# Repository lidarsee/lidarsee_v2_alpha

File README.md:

# LIDARsee v2 Hardware 

A good summary of the _Neato XV-11 LIDAR module_ can be found at:  
http://blog.tkjelectronics.dk/2014/08/handheld-xv-11-lidar-with-stm32f429-and-matlab/

## License
**Hardware license**: Creative Commons CC0
https://creativecommons.org/publicdomain/zero/1.0/legalcode

**Software license**: MIT License

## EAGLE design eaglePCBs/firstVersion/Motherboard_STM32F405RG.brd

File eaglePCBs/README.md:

# lidarsee_v2_hardware
Motherboard_STM32F405RG_r1 ist the mainboard for the head unit. 

### Features
* XV-11 lidar compatible
* STM32F405 microprocessor
* ESP32 WiFi/bluetooth-module
* Single cell lipo power supply
* MPU6050 IMU
* We used a single cell 2500mAh LiPo battery

### To Do
* Rework of the LiPo Boost converter (larger inductor?)
* IMU not tested, it is recommended to use an external IMU connected to the I2C port. Soldering the IMU by hand is quite difficult and there are a lot of cheap reliable breakout boards available. For example the BNO055 sensor also delivers easy-to-use Euler's Angles.
* Using parts that can be soldered by hand easierly

## Wiring

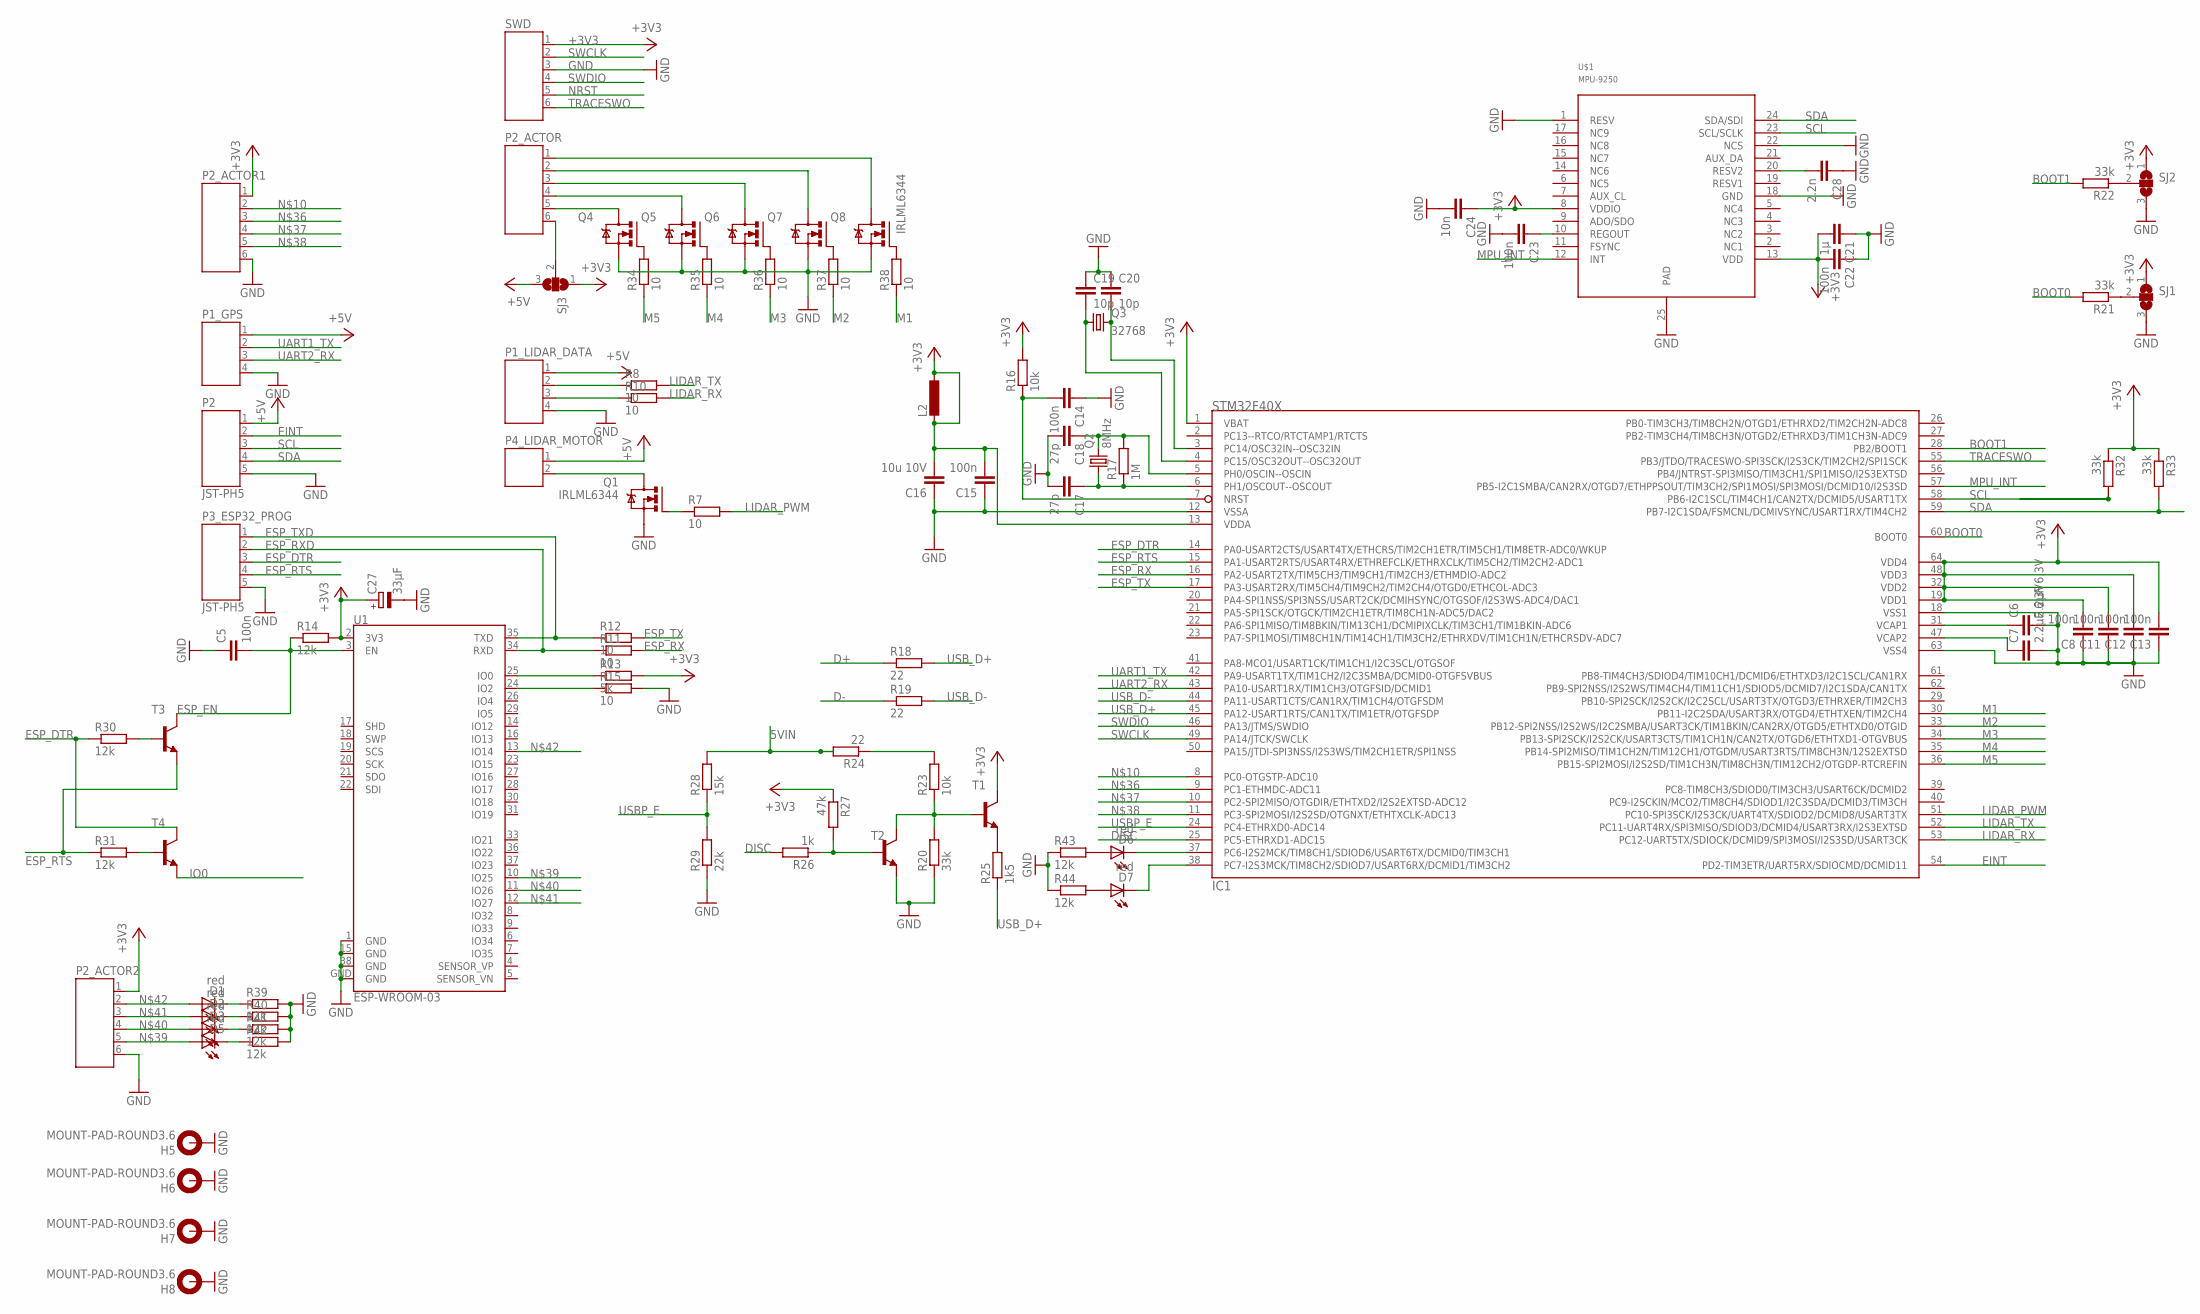
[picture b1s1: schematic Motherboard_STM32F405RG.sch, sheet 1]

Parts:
C5, C8, C11, C12, C13, C14, C15, C22, C23: 100n; C0603; MPN C0603C104K5RACTU
C6, C7: 2.2µF 6.3V; C0603; MPN C0603C225K9PACTU
C16: 10u 10V; C1206; MPN C1206C106K8RACTU
C17, C18: 27p; C0603; MPN CC0603JRNPO9BN270
C19, C20: 10p; C0603; MPN 06035A102JAT2A
C21: 1µ; C0603; MPN 0603YC105KAT2A
C24: 10n; C0603; MPN CC0603KRX7R9BB103
C27: 33µF; A/3216-18W; MPN TPSA336M006R0600
C28: 2.2n; C0603; MPN CC0603KRX7R9BB222
D1, D2, D3, D5, D6, D7: red; LED-0603; MPN LSQ976-Z
H5, H6, H7, H8: MOUNT-PAD-ROUND3.6; 3,6-PAD
IC1: STM32F40X; LQFP64; MPN STM32F405RGT6
L2: L-EUL1812; L1812
P1_GPS, P1_LIDAR_DATA: JST-PH4; MPN B4B-PH-K-S(LF)(SN)
P2, P3_ESP32_PROG: JST-PH5; MPN B5B-PH-K-S(LF)(SN)
P2_ACTOR, P2_ACTOR1, P2_ACTOR2: JST-PH6; MPN B6B-PH-K-S(LF)(SN)
P4_LIDAR_MOTOR: JST-PH2; MPN B2B-PH-K-S(LF)(SN)
Q1, Q4, Q5, Q6, Q7, Q8: IRLML6344; SOT23; MPN IRLML6344TRPBF
Q2: 8MHz; HC18U-V; MPN HC49S-8-30-50-70-30-ATF
Q3: 32768; TC38H; MPN CFS206 32.768KDZB-UB
R7, R8, R10, R11, R12, R15, R34, R35, R36, R37, R38: 10; R0603; MPN CRCW060310R0FKEA
R13: 5k; R0603; MPN CRCW060310R0FKEA
R14: 12k; R0603; MPN CRCW060310R0FKEA
R16: 10k; R0603; MPN CRCW060310R0FKEA
R17: 1M; R0603; MPN CRCW06031M00FKEA
R18, R19, R24: 22; R0603; MPN CRCW060322R0FKEA
R20, R21, R22, R32, R33: 33k; R0603; MPN CRCW060333K0FKEA
R23: 10k; R0603; MPN MCMR06X1002FTL
R25: 1k5; R0603; MPN MCMR06X1501FTL
R26: 1k; R0603; MPN CRCW06031K00FKEA
R27: 47k; R0603; MPN CRCW060347K0FKEA
R28: 15k; R0603; MPN CRCW060315K0FKEA
R29: 22k; R0603; MPN CPF0603F4K22C1
R30, R31, R39, R40, R41, R42, R43, R44: 12k; R0603; MPN MC0063W060312K8
SJ1, SJ2, SJ3: SJ2W; SJ_2
SWD: JST-PH6; MPN B6B-PH-K-S(LF)(SN)
T1, T2, T3, T4: BC817-16-NPN-SOT23-BEC; SOT23-BEC; MPN BC817,215
U1: ESP-WROOM-03
U$1: MPU-9250; LEAD-QFN24; MPN MPU-6050

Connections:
5VIN: R24.2, R28.2; also elsewhere on the board
+3V3: C8.2, C11.2, C12.2, C13.2, C15.2, C16.2, C21.2, C22.2, C24.1, C27.+, IC1.1 (VBAT), IC1.13 (VDDA), IC1.19 (VDD1), IC1.32 (VDD2), IC1.48 (VDD3), IC1.64 (VDD4), L2.1, L2.2, P2_ACTOR1.1, P2_ACTOR2.1, R13.2, R14.2, R16.2, R27.1, R32.1, R33.1, SJ1.1, SJ2.1, SJ3.1, SWD.1, T1.C, U1.2 (3V3), U$1.8 (VDDIO), U$1.13 (VDD); also elsewhere on the board
+5V: P1_GPS.1, P1_LIDAR_DATA.1, P2.1, P4_LIDAR_MOTOR.1, SJ3.3; also elsewhere on the board
BOOT0: IC1.60 (BOOT0), R21.2
BOOT1: IC1.28 (PB2/BOOT1), R22.2
D+: R18.1; also elsewhere on the board
D-: R19.1; also elsewhere on the board
DISC: IC1.25 (PC5-ETHRXD1-ADC15), R26.2
EINT: IC1.54 (PD2-TIM3ETR/UART5RX/SDIOCMD/DCMID11), P2.2
ESP_DTR: IC1.14 (PA0-USART2CTS/USART4TX/ETHCRS/TIM2CH1ET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), P3_ESP32_PROG.3, R30.1, T4.C
ESP_EN: C5.2, R14.1, T3.C, U1.3 (EN)
ESP_RTS: IC1.15 (PA1-USART2RTS/USART4RX/ETHREFCLK/ETHRXC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), P3_ESP32_PROG.4, R31.1, T3.E
ESP_RX: IC1.16 (PA2-USART2TX/TIM5CH3/TIM9CH1/TIM2CH3/ET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), R11.2
ESP_RXD: P3_ESP32_PROG.2, R11.1, U1.34 (RXD)
ESP_TX: IC1.17 (PA3-USART2RX/TIM5CH4/TIM9CH2/TIM2CH4/OT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), R12.2
ESP_TXD: P3_ESP32_PROG.1, R12.1, U1.35 (TXD)
GND: C5.1, C6.2, C7.2, C8.1, C11.1, C12.1, C13.1, C14.1, C15.1, C16.1, C17.2, C18.2, C19.1, C20.1, C21.1, C22.1, C23.2, C24.2, C27.-, C28.1, H5.B3,6, H6.B3,6, H7.B3,6, H8.B3,6, IC1.12 (VSSA), IC1.18 (VSS1), IC1.63 (VSS4), P1_GPS.4, P1_LIDAR_DATA.4, P2.5, P2_ACTOR1.6, P2_ACTOR2.6, P3_ESP32_PROG.5, Q1.2 (S), Q4.2 (S), Q5.2 (S), Q6.2 (S), Q7.2 (S), Q8.2 (S), R15.2, R20.1, R29.1, R39.2, R40.2, R41.2, R42.2, R43.1, R44.1, SJ1.3, SJ2.3, SWD.3, T2.E, U1.1 (GND), U1.15 (GND), U1.38 (GND), U1.GND, U$1.1 (RESV), U$1.18 (GND), U$1.22 (NCS), U$1.25 (PAD); also elsewhere on the board
IO0: R13.1, T4.E, U1.25 (IO0)
IO2: R15.1, U1.24 (IO2)
LIDAR_PWM: IC1.51 (PC10-SPI3SCK/I2S3CK/UART4TX/SDIOD2/DCMI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), R7.2
LIDAR_RX: IC1.53 (PC12-UART5TX/SDIOCK/DCMID9/SPI3MOSI/I2S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), R10.2
LIDAR_TX: IC1.52 (PC11-UART4RX/SPI3MISO/SDIOD3/DCMID4/USA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), R8.2
M1: IC1.30 (PB11-I2C2SDA/USART3RX/OTGD4/ETHTXEN/TIM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), R38.1
M2: IC1.33 (PB12-SPI2NSS/I2S2WS/I2C2SMBA/USART3CK/T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), R37.1
M3: IC1.34 (PB13-SPI2SCK/I2S2CK/USART3CTS/TIM1CH1N/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), R36.1
M4: IC1.35 (PB14-SPI2MISO/TIM1CH2N/TIM12CH1/OTGDM/U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), R35.1
M5: IC1.36 (PB15-SPI2MOSI/I2S2SD/TIM1CH3N/TIM8CH3N/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), R34.1
MPU_INT: IC1.57 (PB5-I2C1SMBA/CAN2RX/OTGD7/ETHPPSOUT/TIM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), U$1.12 (INT)
unnamed: C28.2, U$1.20 (RESV2)
unnamed: P4_LIDAR_MOTOR.2, Q1.3 (D)
unnamed: Q1.1 (G), R7.1
unnamed: P1_LIDAR_DATA.2, R8.1
unnamed: P1_LIDAR_DATA.3, R10.1
unnamed: C23.1, U$1.10 (REGOUT)
unnamed: IC1.8 (PC0-OTGSTP-ADC10), P2_ACTOR1.2
unnamed: P2_ACTOR.5, Q4.3 (D)
unnamed: R31.2, T4.B
unnamed: P2_ACTOR.4, Q5.3 (D)
unnamed: C17.1, IC1.6 (PH1/OSCOUT--OSCOUT), Q2.1, R17.1
unnamed: P2_ACTOR.3, Q6.3 (D)
unnamed: P2_ACTOR.2, Q7.3 (D)
unnamed: C18.1, IC1.5 (PH0/OSCIN--OSCIN), Q2.2, R17.2
unnamed: C19.2, IC1.4 (PC15/OSC32OUT--OSC32OUT), Q3.1
unnamed: C20.2, IC1.3 (PC14/OSC32IN--OSC32IN), Q3.2
unnamed: R20.2, R23.1, T1.B, T2.C
unnamed: R21.1, SJ1.2
unnamed: R22.1, SJ2.2
unnamed: P2_ACTOR.1, Q8.3 (D)
unnamed: R25.2, T1.E
unnamed: R23.2, R24.1
unnamed: R26.1, R27.2, T2.B
unnamed: R30.2, T3.B
unnamed: P2_ACTOR.6, SJ3.2
unnamed: Q4.1 (G), R34.2
unnamed: Q5.1 (G), R35.2
unnamed: Q6.1 (G), R36.2
unnamed: Q7.1 (G), R37.2
unnamed: Q8.1 (G), R38.2
unnamed: IC1.9 (PC1-ETHMDC-ADC11), P2_ACTOR1.3
unnamed: IC1.10 (PC2-SPI2MISO/OTGDIR/ETHTXD2/I2S2EXTSD-A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), P2_ACTOR1.4
unnamed: IC1.11 (PC3-SPI2MOSI/I2S2SD/OTGNXT/ETHTXCLK-ADC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), P2_ACTOR1.5
unnamed: D5.A, P2_ACTOR2.5, U1.10 (IO25)
unnamed: D3.A, P2_ACTOR2.4, U1.11 (IO26)
unnamed: D2.A, P2_ACTOR2.3, U1.12 (IO27)
unnamed: D1.A, P2_ACTOR2.2, U1.13 (IO14)
unnamed: D1.C, R39.1
unnamed: D2.C, R40.1
unnamed: D3.C, R41.1
unnamed: D5.C, R42.1
unnamed: D6.C, IC1.37 (PC6-I2S2MCK/TIM8CH1/SDIOD6/USART6TX/DCM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)
unnamed: D7.C, IC1.38 (PC7-I2S3MCK/TIM8CH2/SDIOD7/USART6RX/DCM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)
unnamed: D6.A, R43.2
unnamed: D7.A, R44.2
NRST: C14.2, IC1.7 (NRST), R16.1, SWD.5
SCL: IC1.58 (PB6-I2C1SCL/TIM4CH1/CAN2TX/DCMID5/USART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), P2.3, R32.2, U$1.23 (SCL/SCLK)
SDA: IC1.59 (PB7-I2C1SDA/FSMCNL/DCMIVSYNC/USART1RX/T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), P2.4, R33.2, U$1.24 (SDA/SDI)
SWCLK: IC1.49 (PA14/JTCK/SWCLK), SWD.2
SWDIO: IC1.46 (PA13/JTMS/SWDIO), SWD.4
TRACESWO: IC1.55 (PB3/JTDO/TRACESWO-SPI3SCK/I2S3CK/TIM2CH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), SWD.6
UART1_TX: IC1.42 (PA9-USART1TX/TIM1CH2/I2C3SMBA/DCMID0-OT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), P1_GPS.2
UART2_RX: IC1.43 (PA10-USART1RX/TIM1CH3/OTGFSID/DCMID1), P1_GPS.3
USBP_E: IC1.24 (PC4-ETHRXD0-ADC14), R28.1, R29.2
USB_D+: IC1.45 (PA12-USART1RTS/CAN1TX/TIM1ETR/OTGFSDP), R18.2, R25.1
USB_D-: IC1.44 (PA11-USART1CTS/CAN1RX/TIM1CH4/OTGFSDM), R19.2
VCAP1: C6.1, IC1.31 (VCAP1)
VCAP2: C7.1, IC1.47 (VCAP2)

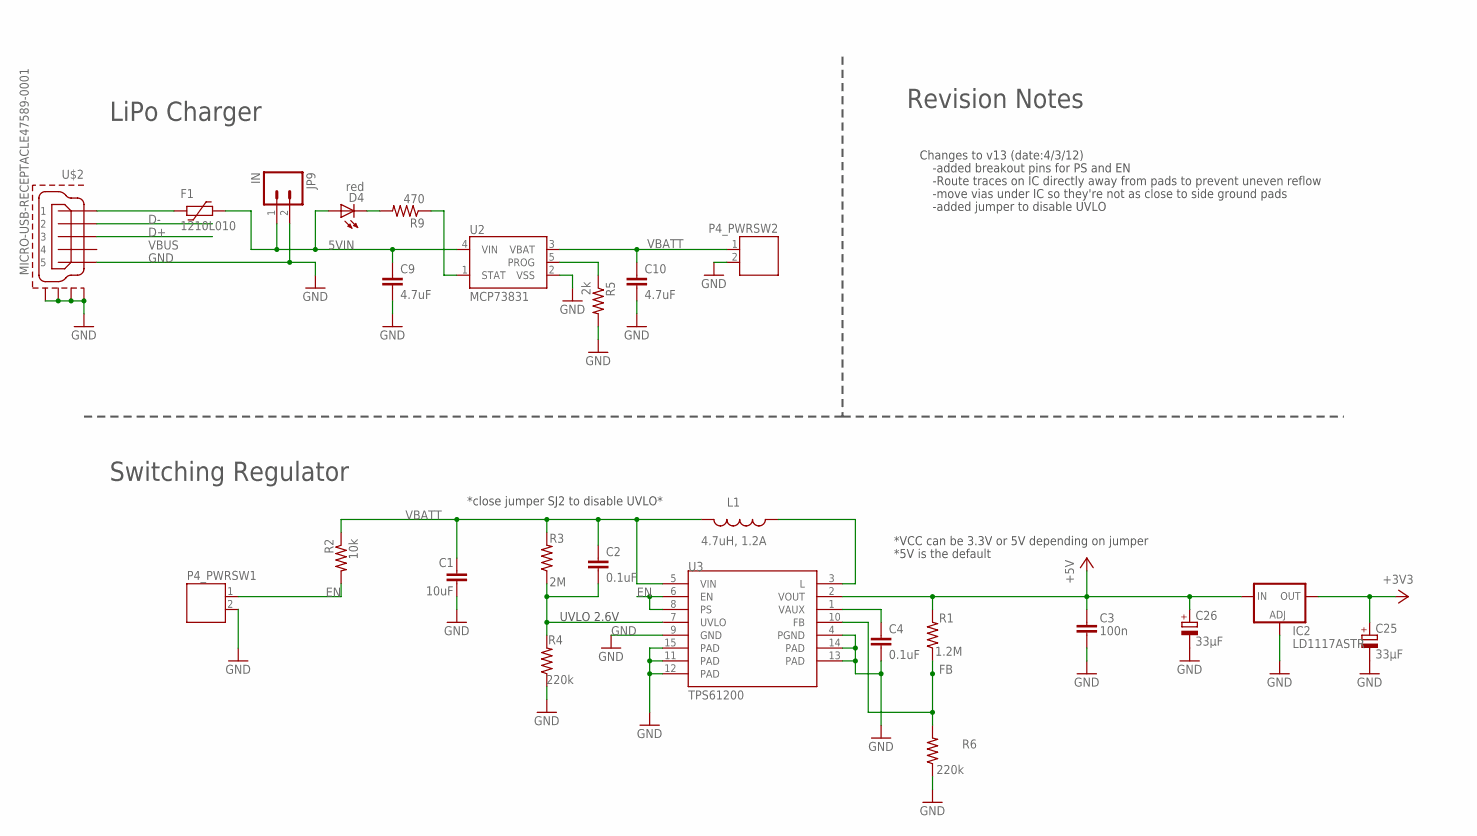
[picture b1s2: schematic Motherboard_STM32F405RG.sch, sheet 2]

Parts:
C1: 10uF; 1206; MPN C1206C106K8RACTU
C2, C4: 0.1uF; 0603-CAP; MPN CC0603MRY5V9BB104
C3: 100n; 0805; MPN C0603C104K5RACTU
C9, C10: 4.7uF; 0603-CAP; MPN C0603C475K8PACTU
C25, C26: 33µF; A/3216-18W; MPN TPSA336M006R0600
D4: red; LED-0603; MPN LSQ976-Z
F1: 1210L010; 1210L; MPN 1210L010WR
IC2: LD1117ASTR; SOT223; MPN NCP1117ST33T3G
JP9: IN; 1X02; MPN B2B-PH-K-S(LF)(SN)
L1: 4.7uH, 1.2A; CDRH2D09; MPN LQH3NPN4R7MJ0L
P4_PWRSW1, P4_PWRSW2: JST-PH2; MPN B2B-PH-K-S(LF)(SN)
R1: 1.2M; 0603-RES; MPN MCMR06W2004FTL
R2: 10k; 0603-RES; MPN MCMR06X1002FTL
R3: 2M; 0603-RES; MPN RK73H1JTTD1204F
R4, R6: 220k; 0603-RES; MPN MCHP03W8F2203T5E
R5: 2k; 0603-RES; MPN RC0603FR-072K2L.
R9: 470; 0603-RES; MPN MCHP03W8F4700T5E
U2: MCP73831; SOT23-5; MPN MCP73831T-2ACI/OT
U3: TPS61200; QFN-10_PAD; MPN TPS61200DRCT
U$2: MICRO-USB-RECEPTACLE47589-0001; 47589-0001; MPN 47589-0001

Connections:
5VIN: C9.1, D4.A, F1.1, JP9.1, U2.4 (VIN); also elsewhere on the board
+3V3: C25.+, IC2.2 (OUT), IC2.4 (OUT); also elsewhere on the board
+5V: C3.1, C26.+, IC2.3 (IN), R1.2, U3.2 (VOUT); also elsewhere on the board
D+: U$2.3; also elsewhere on the board
D-: U$2.2; also elsewhere on the board
EN: P4_PWRSW1.1, R2.2, U3.6 (EN), U3.8 (PS)
FB: R1.1, R6.2, U3.10 (FB)
GND: C1.2, C3.2, C4.2, C9.2, C10.2, C25.-, C26.-, IC2.1 (ADJ), JP9.2, P4_PWRSW1.2, P4_PWRSW2.2, R4.1, R5.2, R6.1, U2.2 (VSS), U3.4 (PGND), U3.9 (GND), U3.11 (PAD), U3.12 (PAD), U3.13 (PAD), U3.14 (PAD), U3.15 (PAD), U$2.5, U$2.CASING1 (GND1), U$2.CASING2 (GND2), U$2.CASING3 (GND3), U$2.CASING4 (GND4); also elsewhere on the board
unnamed: C4.1, U3.1 (VAUX)
unnamed: L1.P$1 (1), U3.3 (L)
unnamed: D4.C, R9.2
unnamed: R5.1, U2.5 (PROG)
unnamed: R9.1, U2.1 (STAT)
UVLO: C2.2, R3.1, R4.2, U3.7 (UVLO)
VBATT: C1.1, C2.1, C10.1, L1.P$2 (2), P4_PWRSW2.1, R2.1, R3.2, U2.3 (VBAT), U3.5 (VIN)
VBUS: F1.2, U$2.1

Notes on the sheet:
UVLO 2.6V
Changes to v13 (date:4/3/12)
-added breakout pins for PS and EN
-Route traces on IC directly away from pads to prevent uneven reflow
-move vias under IC so they're not as close to side ground pads
*close jumper SJ2 to disable UVLO*
-added jumper to disable UVLO
LiPo Charger
Switching Regulator
Revision Notes
*VCC can be 3.3V or 5V depending on jumper
*5V is the default

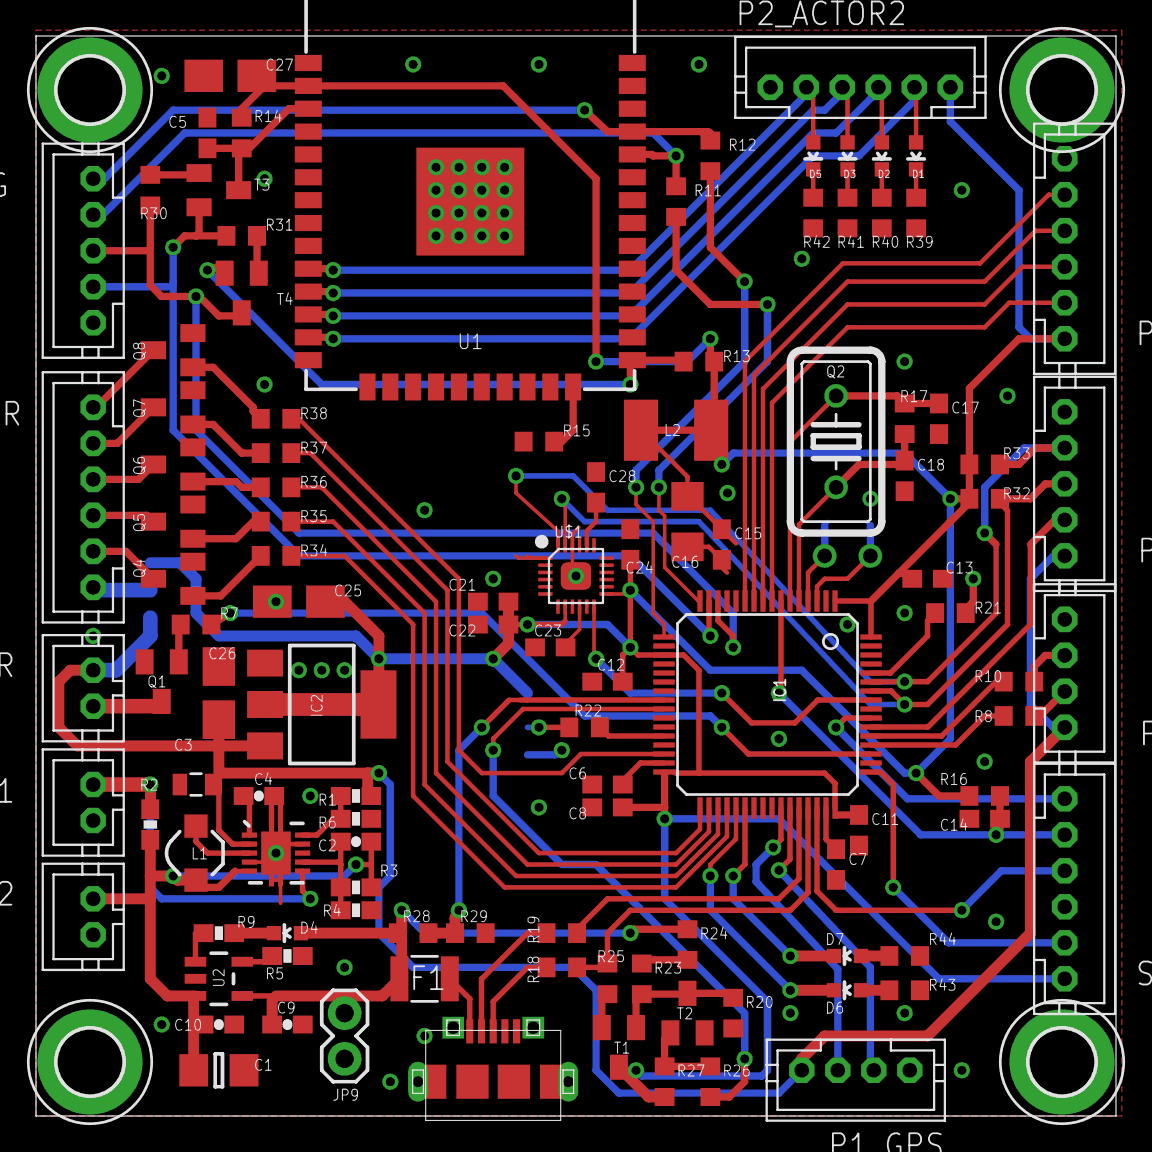
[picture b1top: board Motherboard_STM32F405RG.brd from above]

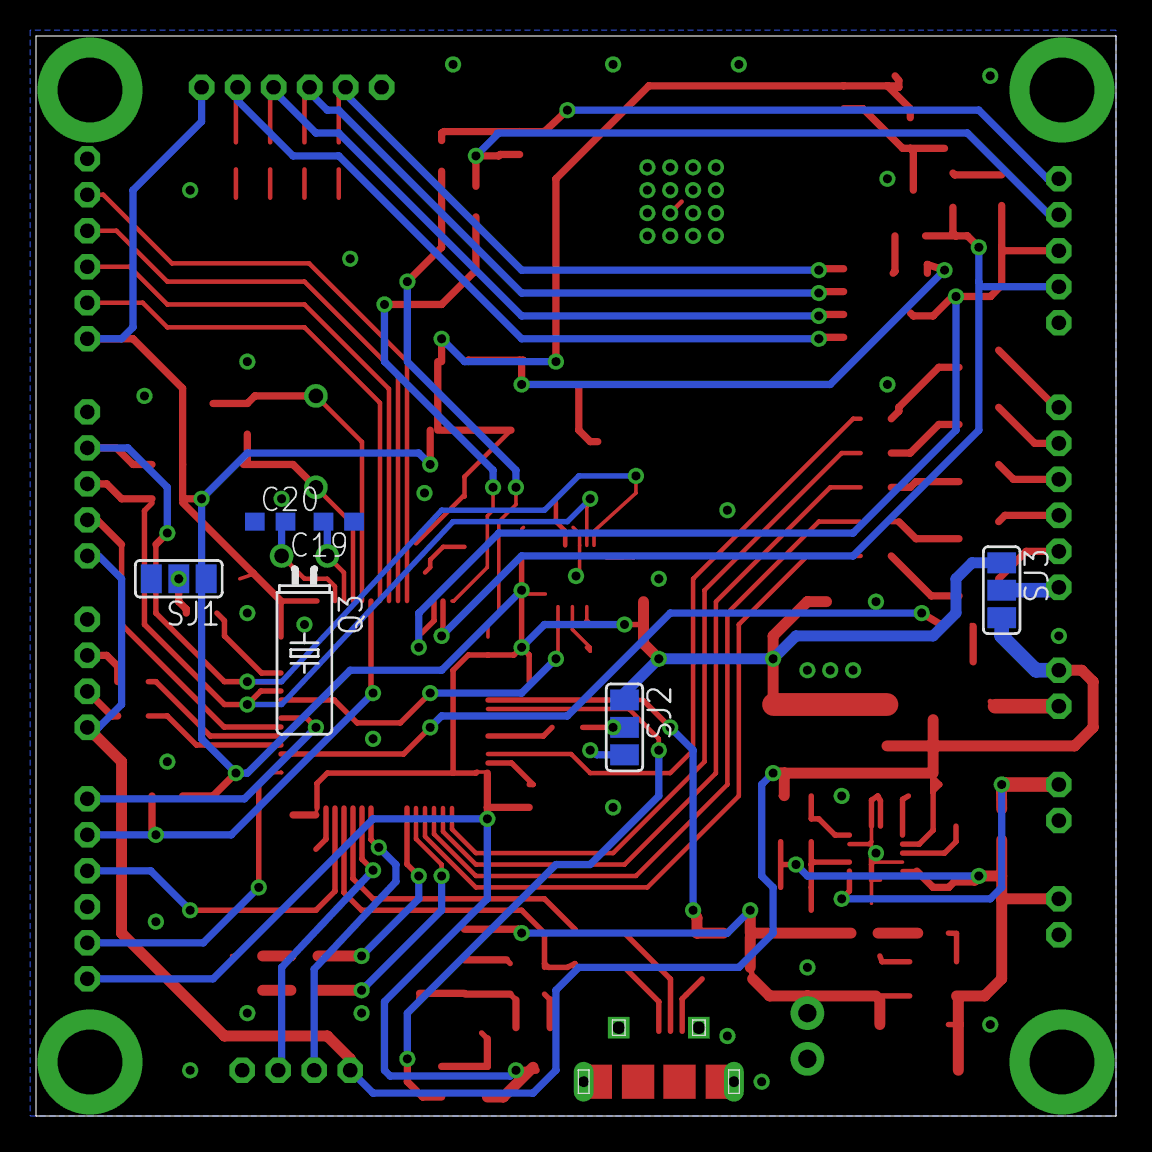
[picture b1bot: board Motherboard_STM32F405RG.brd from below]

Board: 2 copper layers, 60.0 x 60.0 mm, 120 parts (6 on the bottom side), 96 nets.

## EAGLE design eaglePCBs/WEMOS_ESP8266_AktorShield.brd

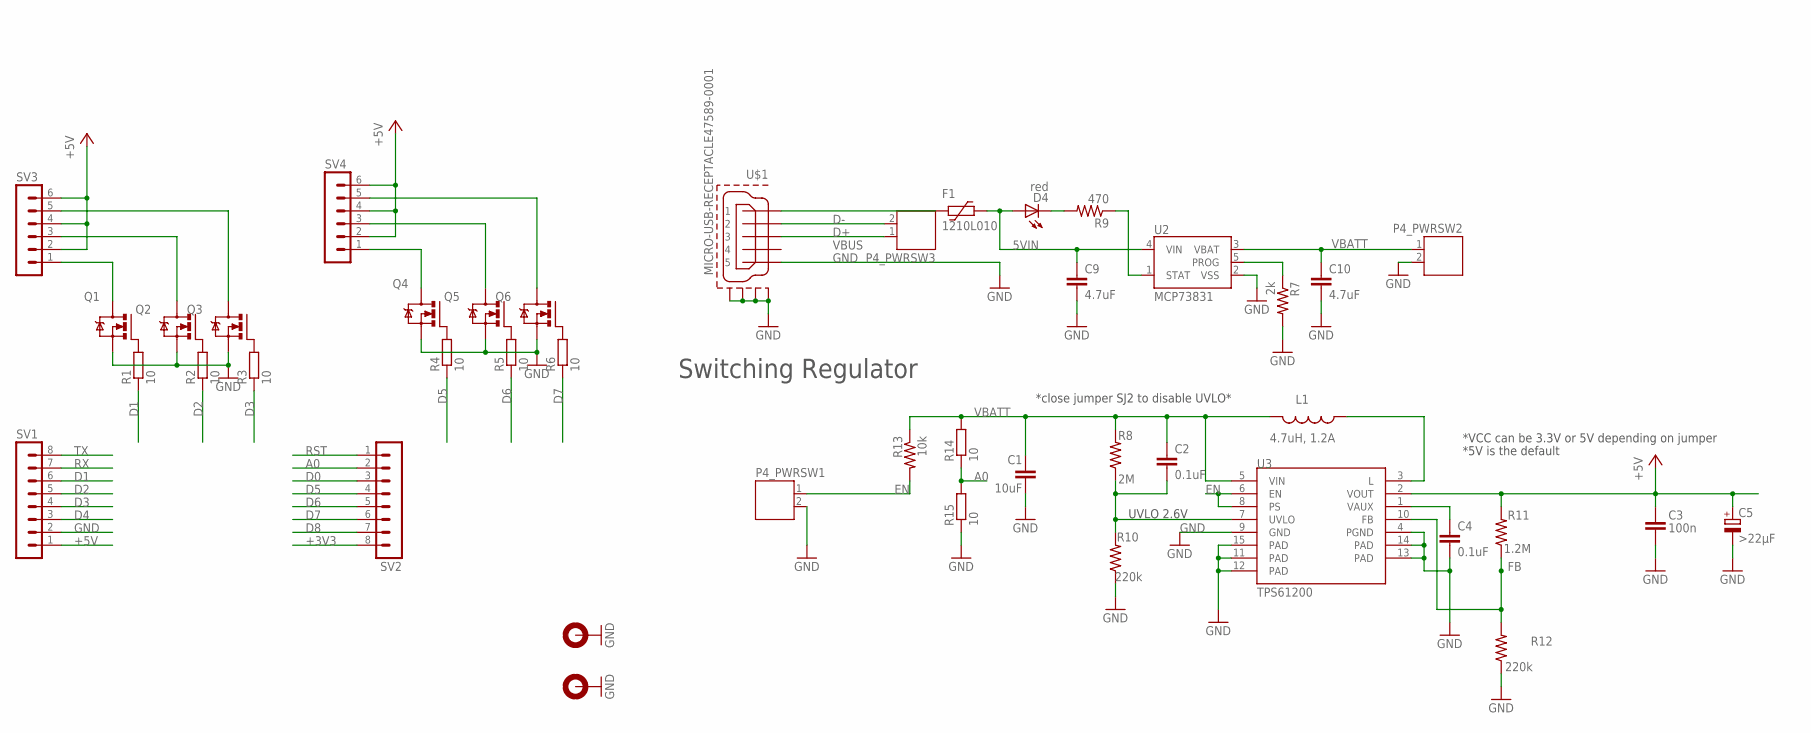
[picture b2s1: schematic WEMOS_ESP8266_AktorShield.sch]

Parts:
C1: 10uF; 1206; MPN C1206C106K8RACTU
C2, C4: 0.1uF; 0603-CAP; MPN CC0603MRY5V9BB104
C3: 100n; 0805; MPN CC0603MRY5V9BB104
C5: >22µF; SMC_C
C9, C10: 4.7uF; 0603-CAP; MPN C0603C475K8PACTU
D4: red; LED-0603; MPN LSQ976-Z
F1: 1210L010; 1210L; MPN 1210L010WR
H7, H8: MOUNT-PAD-ROUND3.6; 3,6-PAD
L1: 4.7uH, 1.2A; CDRH2D09; MPN LQH3NPN4R7MJ0L
P4_PWRSW1, P4_PWRSW2, P4_PWRSW3: JST-PH2; MPN B2B-PH-K-S(LF)(SN)
Q1, Q2, Q3, Q4, Q5, Q6: IRLML6344; SOT23; MPN IRLML6344TRPBF
R1, R2, R3, R4, R5, R6, R14, R15: 10; R0603; MPN CRCW060310R0FKEA
R7: 2k; 0603-RES; MPN RC0603FR-072K2L.
R8: 2M; 0603-RES; MPN RK73H1JTTD1204F
R9: 470; 0603-RES; MPN MCHP03W8F4700T5E
R10, R12: 220k; 0603-RES; MPN MCHP03W8F2203T5E
R11: 1.2M; 0603-RES; MPN MCMR06W2004FTL
R13: 10k; 0603-RES; MPN MCMR06X1002FTL
SV1, SV2: MA08-1SMALL; MA08-1S
SV3, SV4: MA06-1
U2: MCP73831; SOT23-5; MPN MCP73831T-2ACI/OT
U3: TPS61200; QFN-10_PAD; MPN TPS61200DRCT
U$1: MICRO-USB-RECEPTACLE47589-0001; 47589-0001; MPN 47589-0001

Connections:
5VIN: C9.1, D4.A, F1.1, U2.4 (VIN)
+3V3: SV2.8
+5V: C3.1, C5.+, R11.2, SV1.1, SV3.2, SV3.4, SV3.6, SV4.2, SV4.4, SV4.6, U3.2 (VOUT)
A0: R14.1, R15.2, SV2.2
D0: SV2.3
D1: R1.1, SV1.6
D2: R2.1, SV1.5
D3: R3.1, SV1.4
D4: SV1.3
D5: R4.1, SV2.4
D6: R5.1, SV2.5
D7: R6.1, SV2.6
D8: SV2.7
D+: P4_PWRSW3.1, U$1.3
D-: P4_PWRSW3.2, U$1.2
EN: P4_PWRSW1.1, R13.2, U3.6 (EN), U3.8 (PS)
FB: R11.1, R12.2, U3.10 (FB)
GND: C1.2, C3.2, C4.2, C5.-, C9.2, C10.2, H7.B3,6, H8.B3,6, P4_PWRSW1.2, P4_PWRSW2.2, Q1.2 (S), Q2.2 (S), Q3.2 (S), Q4.2 (S), Q5.2 (S), Q6.2 (S), R7.2, R10.1, R12.1, R15.1, SV1.2, U2.2 (VSS), U3.4 (PGND), U3.9 (GND), U3.11 (PAD), U3.12 (PAD), U3.13 (PAD), U3.14 (PAD), U3.15 (PAD), U$1.5, U$1.CASING1 (GND1), U$1.CASING2 (GND2), U$1.CASING3 (GND3), U$1.CASING4 (GND4)
unnamed: Q1.1 (G), R1.2
unnamed: Q2.1 (G), R2.2
unnamed: Q3.1 (G), R3.2
unnamed: Q3.3 (D), SV3.5
unnamed: Q1.3 (D), SV3.1
unnamed: Q2.3 (D), SV3.3
unnamed: Q4.1 (G), R4.2
unnamed: Q5.1 (G), R5.2
unnamed: Q6.1 (G), R6.2
unnamed: Q4.3 (D), SV4.1
unnamed: Q5.3 (D), SV4.3
unnamed: Q6.3 (D), SV4.5
unnamed: R7.1, U2.5 (PROG)
unnamed: R9.1, U2.1 (STAT)
unnamed: D4.C, R9.2
unnamed: L1.P$1 (1), U3.3 (L)
unnamed: C4.1, U3.1 (VAUX)
RST: SV2.1
RX: SV1.7
TX: SV1.8
UVLO: C2.2, R8.1, R10.2, U3.7 (UVLO)
VBATT: C1.1, C2.1, C10.1, L1.P$2 (2), P4_PWRSW2.1, R8.2, R13.1, R14.2, U2.3 (VBAT), U3.5 (VIN)
VBUS: F1.2, U$1.1

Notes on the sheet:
UVLO 2.6V
*close jumper SJ2 to disable UVLO*
Switching Regulator
*VCC can be 3.3V or 5V depending on jumper
*5V is the default

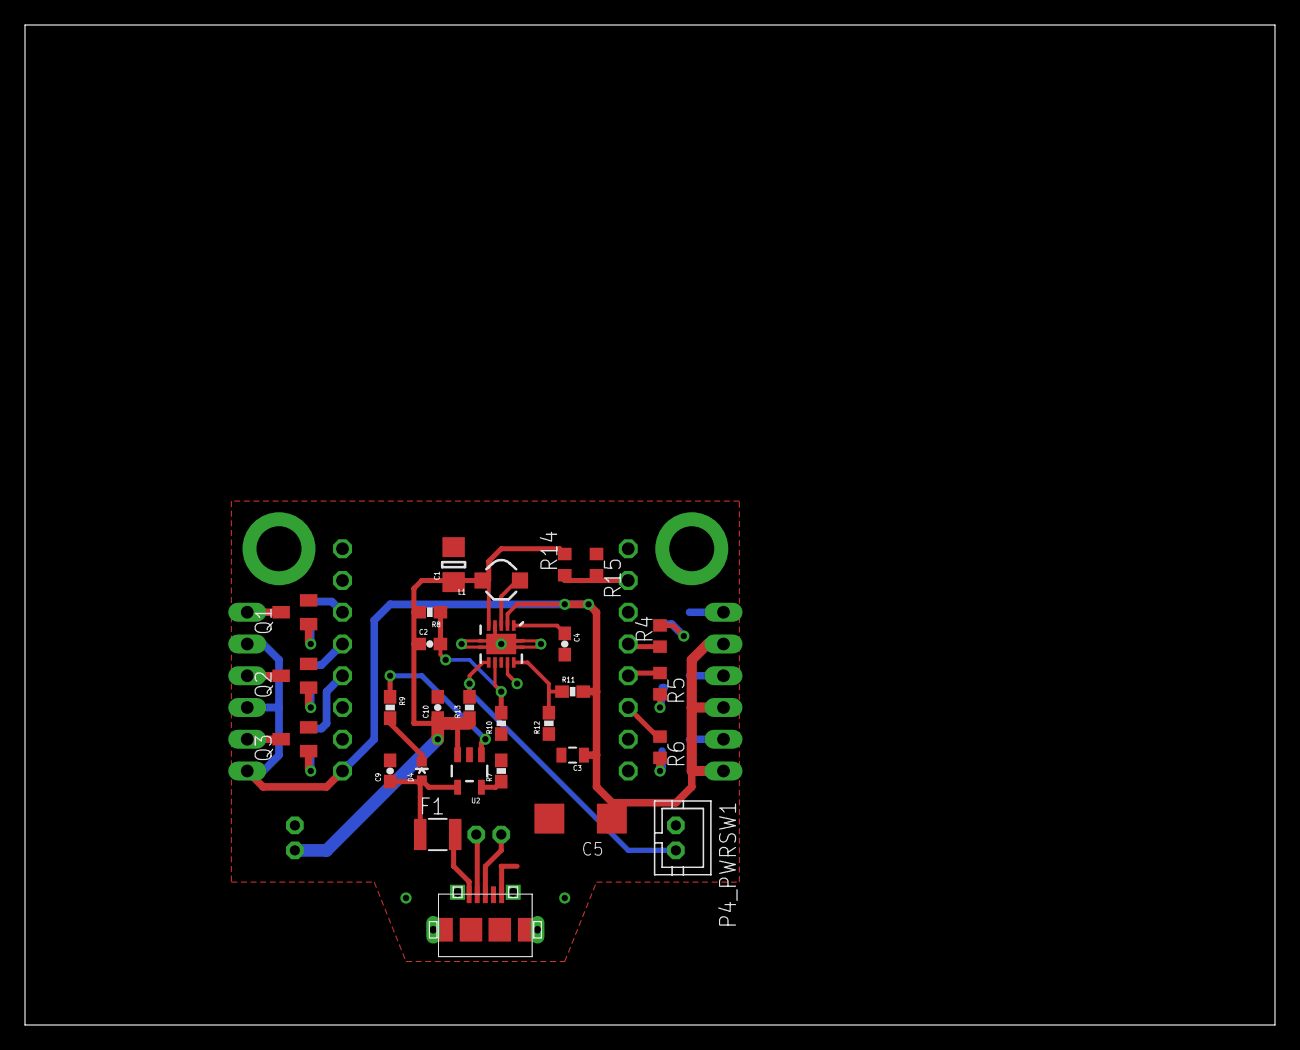
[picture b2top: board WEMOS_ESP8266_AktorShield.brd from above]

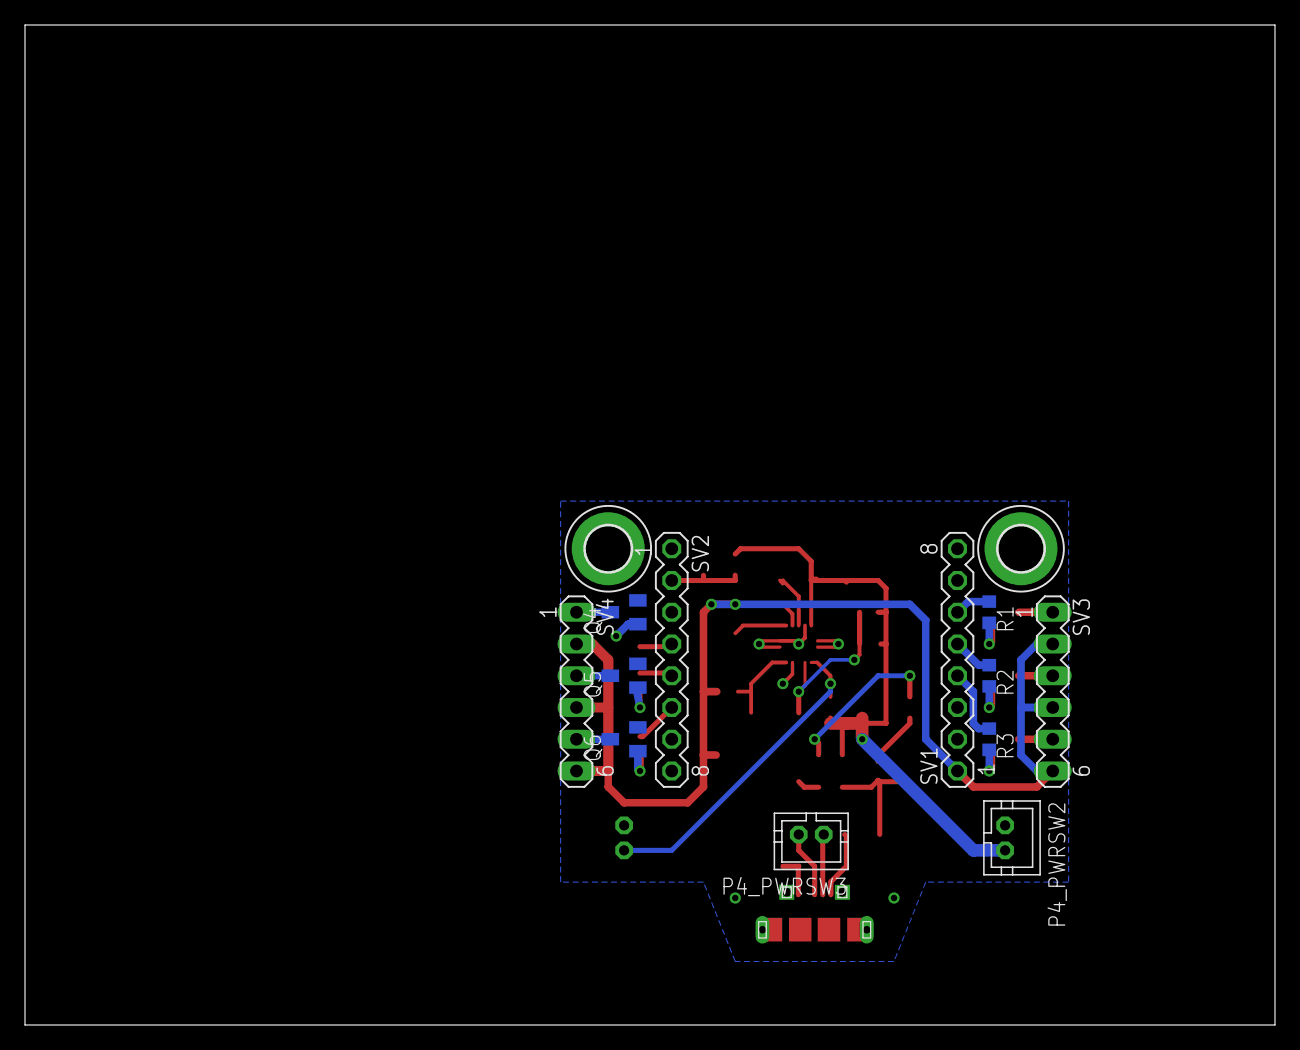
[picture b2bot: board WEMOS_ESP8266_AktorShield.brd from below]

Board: 2 copper layers, 100.0 x 80.0 mm, 43 parts (14 on the bottom side), 34 nets.

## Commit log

2017-08-03 feature freeze
2017-08-03 eagle pcb files
2017-08-07 README added
    clean up
2017-08-07 readme edit
2017-08-07 Wiring image
    readme update
2017-08-08 picture
2017-08-08 License
2017-08-31 compile info
2017-10-12 Groß-/Kleinschreibung, Formatierung
2017-10-12 Formatierung, Parallelisierung

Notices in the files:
parts and their libraries:
con-molex-usb: (C) 2014 Tomasz Boleslaw CEDRO, cederom@tlen.pl, http://www.tomek.cedro.info.
